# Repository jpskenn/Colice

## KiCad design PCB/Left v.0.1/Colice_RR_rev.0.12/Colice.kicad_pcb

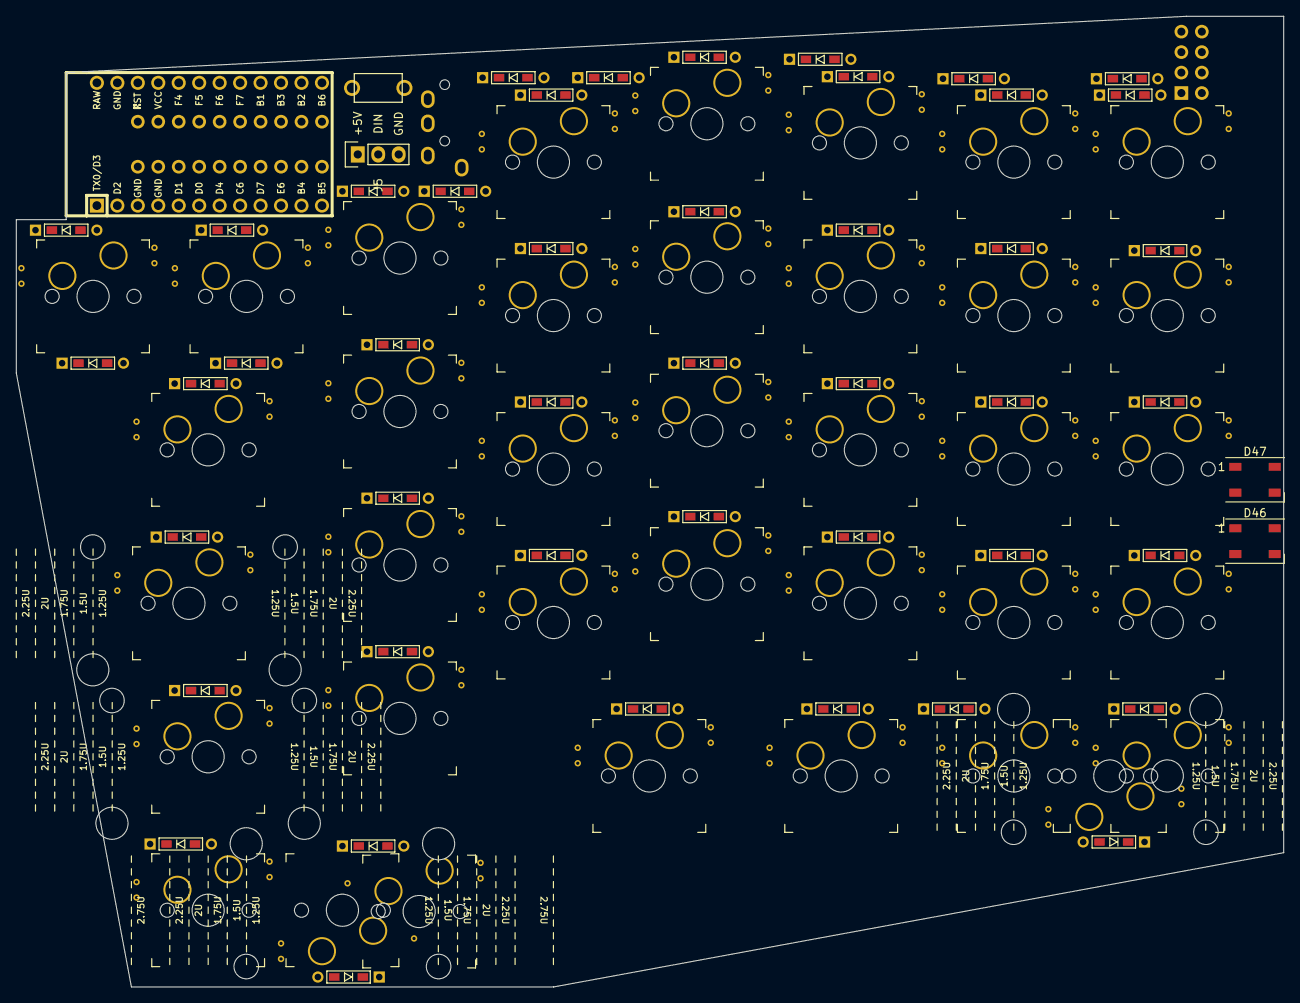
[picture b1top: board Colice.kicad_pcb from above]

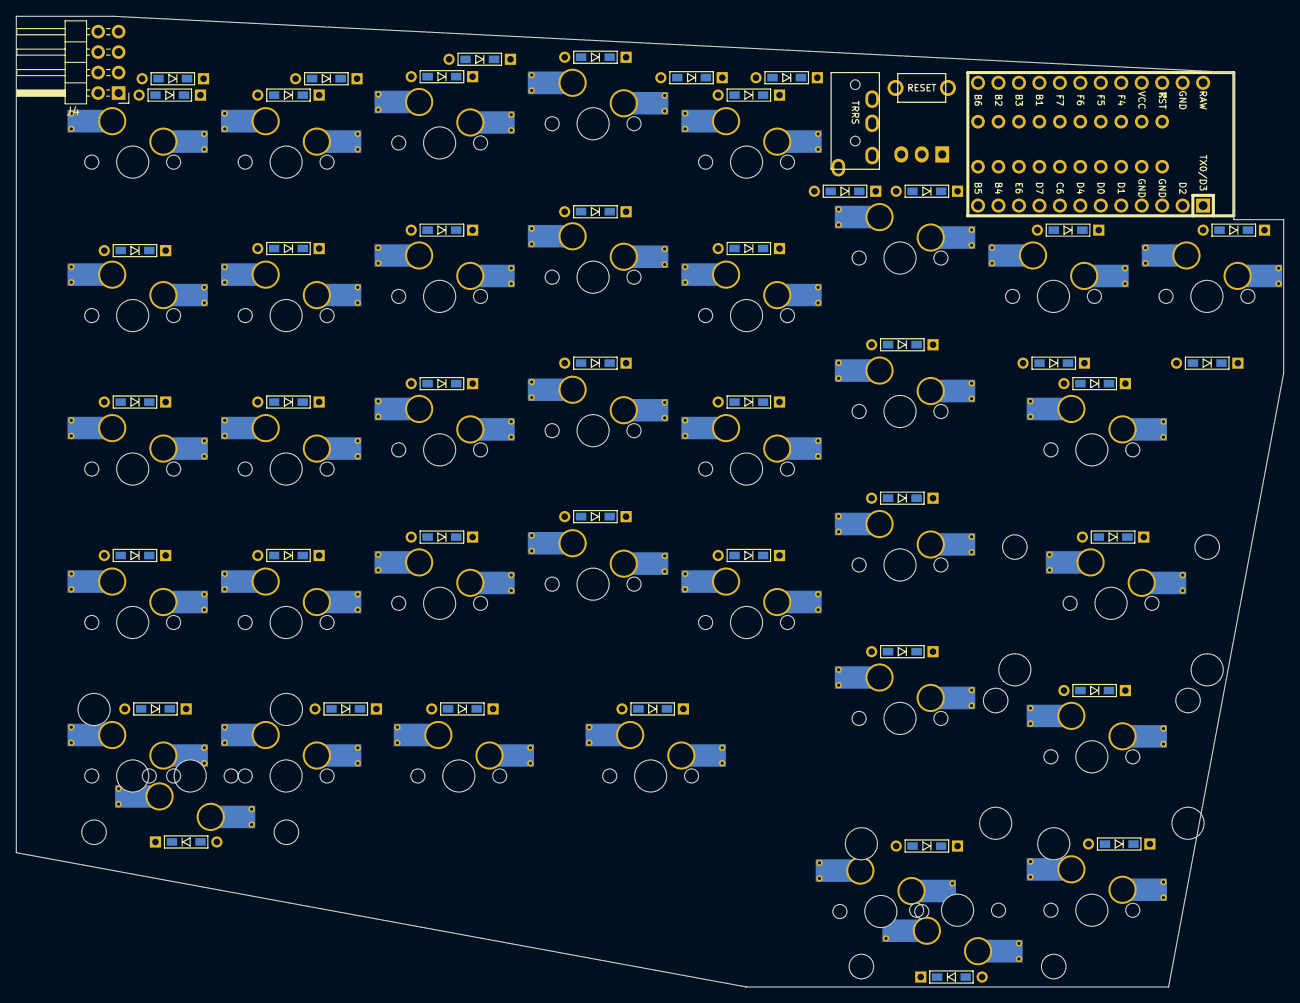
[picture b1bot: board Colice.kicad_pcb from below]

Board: 2 copper layers, 157.3 x 120.5 mm, 93 parts (3 on the bottom side), 67 nets, no tracks yet.

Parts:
D1, D2, D3, D4, D5, D6, D7, D8, D9, D10, D11, D12, D13, D14, D15, D16, D17, D18, D19, D20, D21, D22, D23, D24, D25, D26, D27, D28, D29, D30, D31, D32, D33, D34, D35, D36, D37, D38, D39, D40, D41, D42, D43, D44, D45: D; D3_TH_SMD
D46, D47: WS2812B; LED_WS2812B_PLCC4_5.0x5.0mm_P3.2mm
H1: MountingHole; CherryMX_MidHeight_Choc_Hotswap_2.25U_Outline
H2: MountingHole; CherryMX_MidHeight_Choc_Hotswap_2.75U_Outline
J1, J2: Conn_01x10; PinHeader_1x10_P2.54mm_Vertical
J3: MJ-4PP-9
J4: Conn_02x04_Counter_Clockwise; PinHeader_2x04_P2.54mm_Horizontal
J5: Conn_01x03; Pin_Header_Straight_1x03
SW1: SW_Push; ResetSW
SW2, SW3, SW4, SW5, SW6, SW7, SW8, SW9, SW10, SW11, SW12, SW13, SW14, SW15, SW16, SW17, SW18, SW19, SW20, SW21, SW22, SW23, SW24, SW25, SW26, SW27, SW28, SW29, SW30, SW31, SW32, SW33, SW34, SW35, SW36, SW37, SW38: SW_Push; CherryMX_Hotswap_v2
U1: ProMicro; ArduinoProMicro

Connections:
GND1: D46.3, D47.3, J2.9, J3.C, J5.3, SW1.2, U1.3, U1.4, U1.23
unnamed: D1.1, SW2.1, SW3.1
unnamed: D2.2, SW2.2
unnamed: D3.2, SW3.2
unnamed: D4.1, SW4.1, SW5.1, SW6.1, SW7.1, SW8.1
unnamed: D5.2, SW4.2
unnamed: D6.2, SW5.2
unnamed: D7.2, SW6.2
unnamed: D8.2, SW7.2
unnamed: D9.2, SW8.2
unnamed: D10.1, SW9.1, SW10.1, SW11.1, SW12.1, SW13.1
unnamed: D11.2, SW9.2
unnamed: D12.2, SW10.2
unnamed: D13.2, SW11.2
unnamed: D14.2, SW12.2
unnamed: D15.2, SW13.2
unnamed: D16.1, SW14.1, SW15.1, SW16.1, SW17.1, SW18.1
unnamed: D17.2, SW14.2
unnamed: D18.2, SW15.2
unnamed: D19.2, SW16.2
unnamed: D20.2, SW17.2
unnamed: D21.2, SW18.2
unnamed: D22.1, SW19.1, SW20.1, SW21.1, SW22.1, SW23.1
unnamed: D23.2, SW19.2
unnamed: D24.2, SW20.2
unnamed: D25.2, SW21.2
unnamed: D26.2, SW22.2
unnamed: D27.2, SW23.2
unnamed: D28.1, SW24.1, SW25.1, SW26.1, SW27.1, SW28.1
unnamed: D29.2, SW24.2
unnamed: D30.2, SW25.2
unnamed: D31.2, SW26.2
unnamed: D32.2, SW27.2
unnamed: D33.2, SW28.2
unnamed: D34.1, SW29.1, SW30.1, SW31.1, SW32.1, SW33.1
unnamed: D35.2, SW29.2
unnamed: D36.2, SW30.2
unnamed: D37.2, SW31.2
unnamed: D38.2, SW32.2
unnamed: D39.2, SW33.2
unnamed: D40.1, SW34.1, SW35.1, SW36.1, SW37.1, SW38.1
unnamed: D41.2, SW34.2
unnamed: D42.2, SW35.2
unnamed: D43.2, SW36.2
unnamed: D44.2, SW37.2
unnamed: D45.2, SW38.2
unnamed: D46.2, D47.4
VCC: D46.1, D47.1, J2.10, J3.D, J5.1, U1.21
d4: J1.5, U1.7
data: J1.2, J3.B, U1.2
f4: J2.8, U1.20
f5: J2.7, U1.19
f6: J2.6, U1.18
led: D46.4, J1.1, J5.2, U1.1
pin1: D2.1, D5.1, D11.1, D16.2, J2.5, U1.17
pin2: D6.1, D12.1, D22.2, J2.4, U1.16
pin3: D7.1, D13.1, D28.2, J2.3, U1.15
pin4: D8.1, D14.1, D34.2, J2.2, U1.14
pin5: D3.1, D9.1, D15.1, D40.2, J2.1, U1.13
pin6: D17.1, D23.1, D29.1, D35.1, D41.1, J1.6, J4.1, U1.8
pin7: D18.1, D24.1, D30.1, D36.1, D42.1, J1.7, J4.2, U1.9
pin8: D1.2, D19.1, D25.1, D31.1, D37.1, D43.1, J1.8, J4.3, U1.10
pin9: D4.2, D20.1, D26.1, D32.1, D38.1, D44.1, J1.9, J4.4, U1.11
pin10: D10.2, D21.1, D27.1, D33.1, D39.1, D45.1, J1.10, J4.5, U1.12
reset: SW1.1, U1.22
scl-d0: J1.4, U1.6
sda-d1: J1.3, U1.5
